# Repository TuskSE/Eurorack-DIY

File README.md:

View this project on [CADLAB.io](https://cadlab.io/project/24780). 

# Eurorack DIY
 An assortment of Schematics and PCB layouts for synthesizer modules in the Eurorack Format.  PCB layouts mostly use big surface mount parts ( e.g. SOIC IC's, 0804 passives ) except for electrolytics. I try as much as possible to limit the BOM to parts from Tayda Electronics - exceptions are mostly MCU boards and synthesizer-specific ICs. All schematic and PCB files are in KiCAD format, but not all have been updated yet for KiCAD v6. See below for a brief overview of projects.

# Modules

**Bandpass Filter **
A bank of 3 bandpass filters, with options mixing and phase inversion options. Schematics mostly complete, awaiting PCB layout. 

**CP3 Mixer**
A very generic transistor-type mixer. PCB layout complete, awaiting fabrication.

**Dual VCO**
A pair of utility VCOs/LFOs derived from the NonLinearCircuits Dual LFO/VCO, but with added FM inputs ( log on one, lin on the other ) and no sync inputs. PCB layout essentially finished, but I want to go back and rethink the voltage reference before sending it for fabrication.

**Fractional Clock Divider** 
A module to generate fractional divisions/multiplications of a clock signal and euclidean rhythms (which are basically fractional divisions, but quantized). The output can also be delayed / phase shifted. Built around a Teensy LC MCU board. This is "complete" and works, but in practise a lack of visual feedback in the UI makes it unintuitive and not fun to use - at some point I'll build something new and better around the same ideas. 

**Function Generator**
A variation on the Kassutronics slope, which in turn is a variation on the Serge Dual Universal Function Generator. The main notable addition is a hold input. PCB layout complete, awaiting fabrication. 

**Precision multiple**
4 buffered multiples: 2 are high-precision ( i.e. voltage is reproduced accurately enough to use for pitch CV ), all 4 have red/green LED indicators. There are only minor problems with the current PCB ( e.g. two of the LED footprints are the wrong way round ). 

**Threshold Logic Neuron** 
A Threshold Logic Neuron ( McCulloch–Pitts neuron ), inspired by a module from Analogue Research. In addition to serving as a programmable logic gate, the internal summing node has a dedicated output which can be used for the generation of stepwise CVs from boolean inputs. PCB layout just needs double-checking - otherwise, awaiting fabrication. 

**Precision Attenuverter**
A utility set of 4x attenuverters and cascading mixer, a.la fonitronik cascade. The first input can be calibrated so that "1x" attenuation ( knob fully CW ) is precise enough to use for pitch CV. The first batch of these had some PCB errors ( hard-to-solder footprints, back-to-front pots, etc ) which should be fixed in the current design ( March 2021 ), but I haven't fabbed it yet. I think the knob spacing is too tight - I plan to redo the layout with a wider spacing. 

**Stochastic sequencer**
A huge voltage sequencer project, incorporating elements of repeatable randomness ( like shift-register based sequencers ) and multiple steps per stage ( like the M185 sequencer / Intellijel Metropolis ). Each stage has its own independent voltage output, and the outputs are summed cascade-style until an input is plugged in. Multiple cycles can run in parallel over the 8 stages. The current version of the PCB ( v2 ) is working in terms of core functionality, but needs some minor tweaks. Most of the functionality is coded up, but after writing 1000s of lines of code I realized that the MCU ( Teensy LC ) RAM is insufficient for the functionality that I want, especially with regards to repeatable randomness. I believe the chip for the capacitive touch interface has also gone out of production. I'm still undecided whether to try again with a different MCU + capacitive touch chip, or whether to break the design up into smaller independent modules. 

**Tap LFO**
A clock-synced LFO built around the Electric Druid Tap LFO IC. The current version of the PCB layout only needs some small revisions, however I've abandoned it for now - in practise, I think it requires more visual feedback than can be accommodated with the Electric Druid IC. 

**Quad VCA**
A quad VCA built around the V2164 IC. Each channel has 2 CV attenuverters, one normalized to a 5V input. There's also a panning mixer integrated. v1 of the PCB had a couple of major issues which are awaiting correction. I think I may also rethink the control ranges etc.

**Pedal interface**
Designed as an interface between Eurorack and guitar pedals - schematic still under development. 

**Random trigger generator**
Barely started - still at the UI design phase 
 
# Case designs:

**"Big" case**
A console style case, 2 x 3U x 120HP, with space on top to mount more more cases.
Designed for laser cut 12mm plywood and standard Gie-tec rails.
I've built one of these - the glue up was a bit awkward with the non-square angle of the front piece, but otherwise it works fine and seems very solid. 

**"Test" case**
An 85HP rack with panel cutouts for current monitors and convenient terminals for oscilloscope/multimeter probes. In retrospect this is kind of a dumb idea when these things could have been added as, y'know, modules. A 1U row along the bottom instead would have been nice.
Designed for and laser cut from 5mm bamboo ply, which is attractive but honestly a bit flimsy, especially accross the grain.

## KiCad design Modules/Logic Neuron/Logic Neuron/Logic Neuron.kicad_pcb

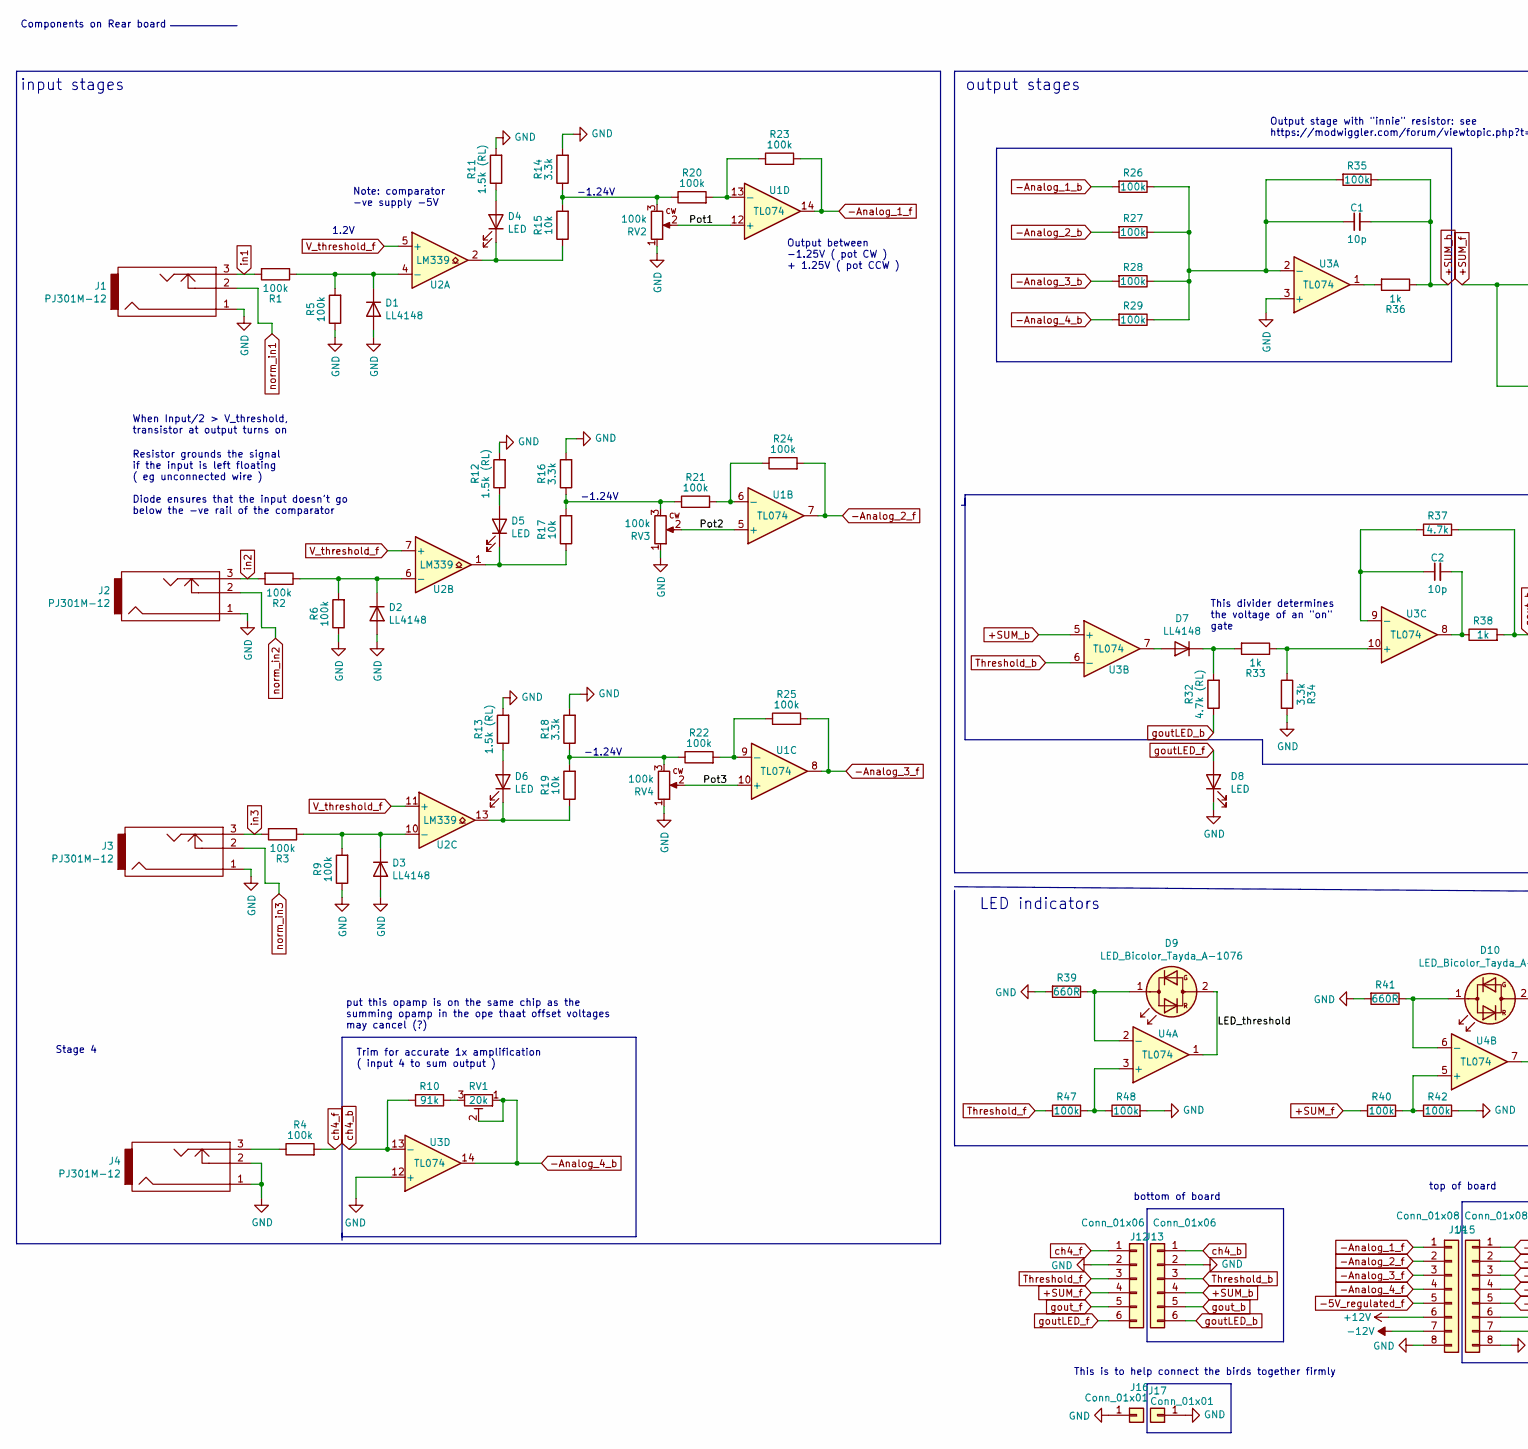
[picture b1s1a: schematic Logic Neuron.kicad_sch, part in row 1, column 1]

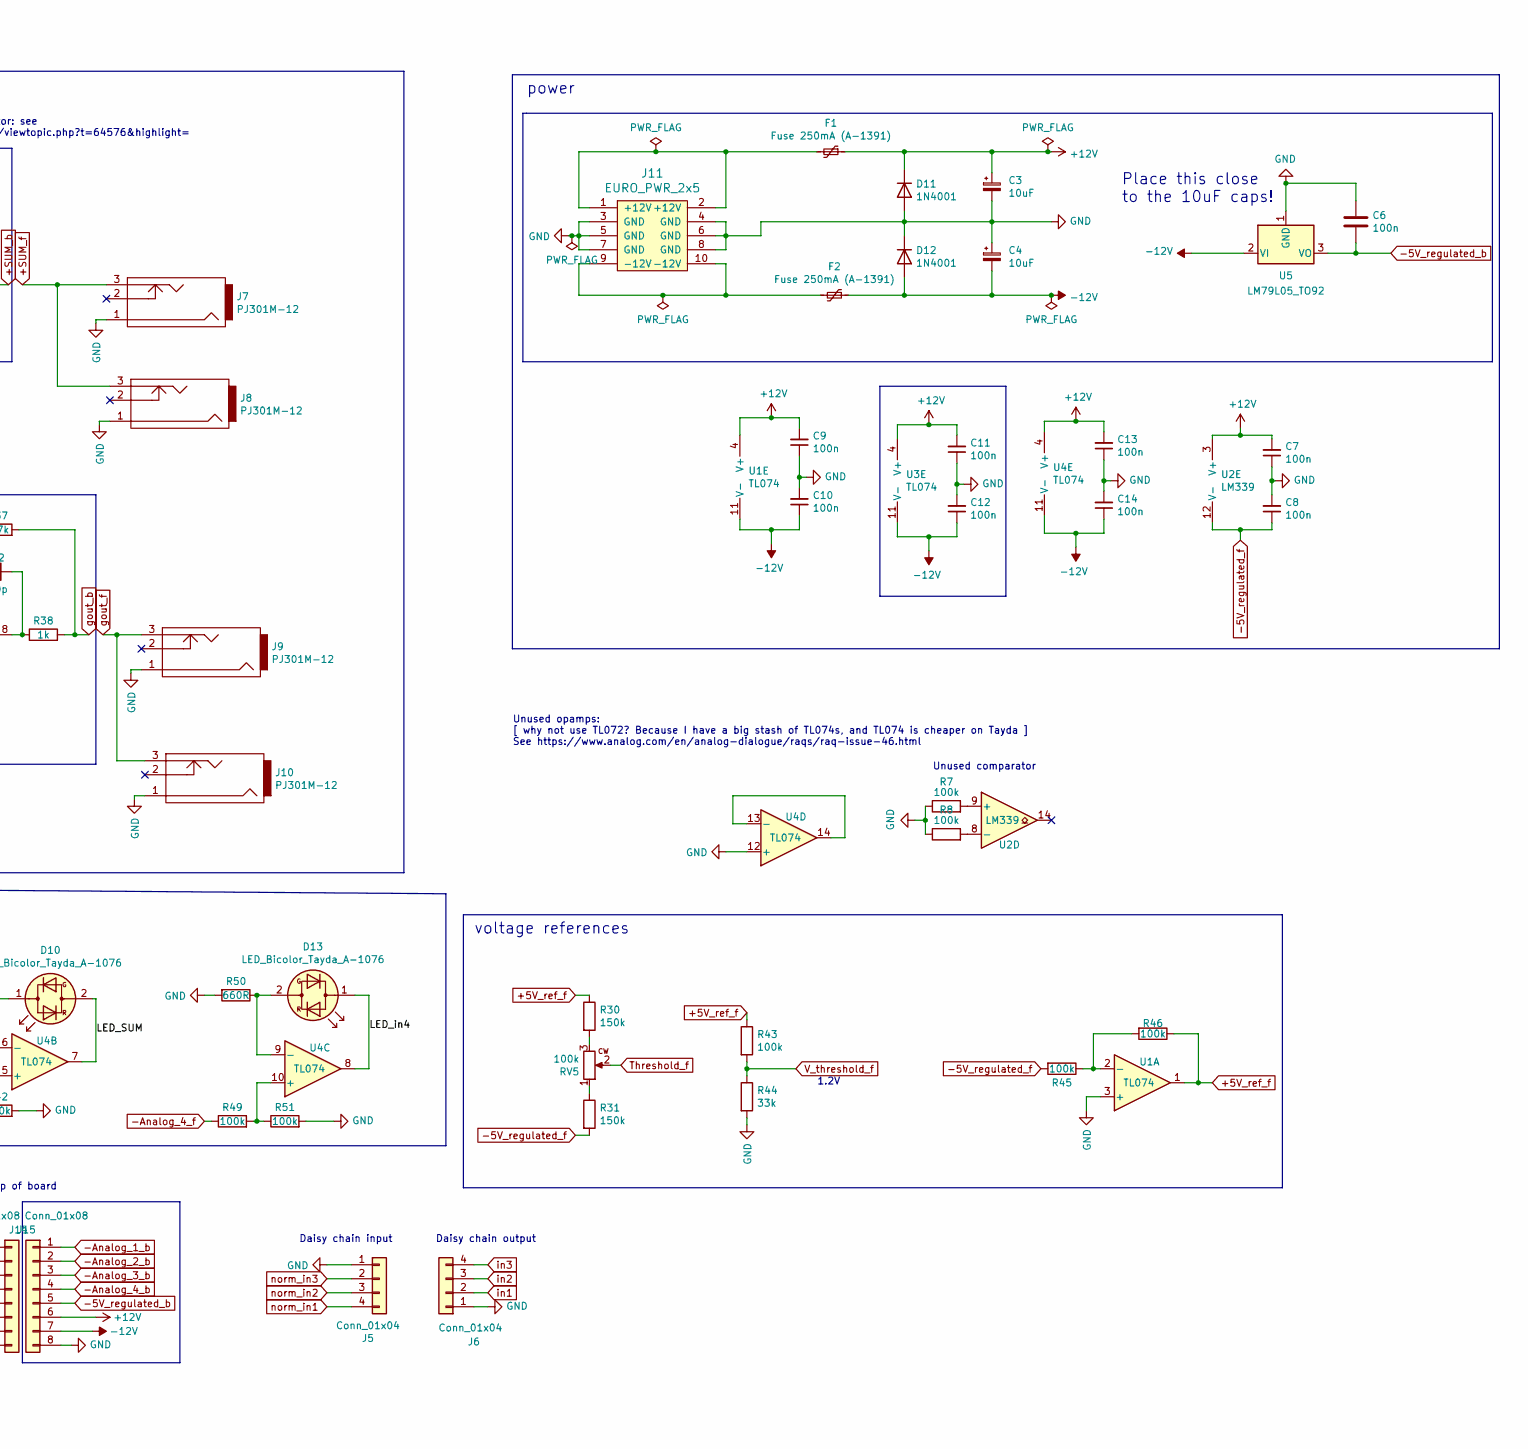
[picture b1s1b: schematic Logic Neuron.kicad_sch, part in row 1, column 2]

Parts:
C1, C2: 10p; C_0805_2012Metric_Pad1.15x1.40mm_HandSolder_SmallTxt
C3, C4: 10uF; CP_Radial_D5.0mm_P2.00mm
C6, C7, C8, C9, C10, C11, C12, C13, C14: 100n; C_0805_2012Metric_Pad1.15x1.40mm_HandSolder_SmallTxt
D1, D2, D3, D7: LL4148; LL4148_sam
D4, D5, D6, D8: LED; LED3mm
D9, D10, D13: LED_Bicolor_Tayda_A-1076; TaydaA-1076_bicolor_LED
D11, D12: 1N4001; D_DO-41_SOD81_P10.16mm_Horizontal
F1, F2: Fuse 250mA (A-1391); C_Disc_D7.5mm_W2.5mm_P5.00mm
J1, J2, J3, J4, J7, J8, J9, J10: PJ301M-12; PJ301M-12_Compact
J5, J6: Conn_01x04; PinHeader_1x04_P2.54mm_Vertical
J11: EURO_PWR_2x5; Eurorack_power_header
J12, J13: Conn_01x06; PinHeader_1x06_P2.54mm_Vertical
J14, J15: Conn_01x08; PinHeader_1x08_P2.54mm_Vertical
J16, J17: Conn_01x01; PinSocket_1x01_P2.54mm_Vertical
R1, R2, R3, R4, R5, R6, R7, R8, R9, R20, R21, R22, R23, R24, R25, R26, R27, R28, R29, R35, R40, R42, R43, R45, R46, R47, R48, R49, R51: 100k; R_0805_2012Metric_Pad1.15x1.40mm_HandSolder_smallText
R10: 91k; R_0805_2012Metric_Pad1.15x1.40mm_HandSolder_smallText
R11, R12, R13: 1.5k (RL); R_0805_2012Metric_Pad1.15x1.40mm_HandSolder_smallText
R14, R16, R18, R34: 3.3k; R_0805_2012Metric_Pad1.15x1.40mm_HandSolder_smallText
R15, R17, R19: 10k; R_0805_2012Metric_Pad1.15x1.40mm_HandSolder_smallText
R30, R31: 150k; R_0805_2012Metric_Pad1.15x1.40mm_HandSolder_smallText
R32: 4.7k (RL); R_0805_2012Metric_Pad1.15x1.40mm_HandSolder_smallText
R33, R36, R38: 1k; R_0805_2012Metric_Pad1.15x1.40mm_HandSolder_smallText
R37: 4.7k; R_0805_2012Metric_Pad1.15x1.40mm_HandSolder_smallText
R39, R41, R50: 660R; R_0805_2012Metric_Pad1.15x1.40mm_HandSolder_smallText
R44: 33k; R_0805_2012Metric_Pad1.15x1.40mm_HandSolder_smallText
RV1: 20k; Potentiometer_Bourns_3296W_Vertical
RV2, RV3, RV4, RV5: 100k; Alpha9mmPot
U1, U3, U4: TL074; SOIC-14_3.9x8.7mm_P1.27mm
U2: LM339; SOIC-14_3.9x8.7mm_P1.27mm
U5: LM79L05_TO92; TO-92_HandSolder

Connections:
+5V_ref_f: R30.1, R43.1, R46.1, U1.1
+12V: C3.1, C7.2, C9.2, C11.2, C13.2, D11.1 (K), F1.1, J14.6, J15.6, U1.4 (V+), U2.3 (V+), U3.4 (V+), U4.4 (V+)
+SUM_b: C1.2, J13.4, R35.1, R36.1, U3.5 (+)
+SUM_f: J7.3, J8.3, J12.4, R40.1
-5V_regulated_b: C6.2, J15.5, U5.3 (VO)
-5V_regulated_f: C8.1, J14.5, R31.2, R45.2, U2.12 (V-)
-12V: C4.2, C10.1, C12.1, C14.1, D12.2 (A), F2.1, J14.7, J15.7, U1.11 (V-), U3.11 (V-), U4.11 (V-), U5.2 (VI)
-Analog_1_b: J15.1, R26.2
-Analog_1_f: J14.1, R23.2, U1.14
-Analog_2_b: J15.2, R27.2
-Analog_2_f: J14.2, R24.2, U1.7
-Analog_3_b: J15.3, R28.2
-Analog_3_f: J14.3, R25.2, U1.8
-Analog_4_b: J15.4, R29.2, RV1.1, RV1.2, U3.14
-Analog_4_f: J14.4, R49.1
/LED_SUM: D10.2 (AK), U4.7
/LED_in4: D13.1 (KA), U4.8
/LED_threshold: D9.2 (AK), U4.1
/Pot1: RV2.2, U1.12 (+)
/Pot2: RV3.2, U1.5 (+)
/Pot3: RV4.2, U1.10 (+)
GND: C3.2, C4.1, C6.1, C7.1, C8.2, C9.1, C10.2, C11.1, C12.2, C13.1, C14.2, D1.2 (A), D2.2 (A), D3.2 (A), D8.1 (K), D11.2 (A), D12.1 (K), J1.1, J2.1, J3.1, J4.1, J4.2, J5.1, J6.1, J7.1, J8.1, J9.1, J10.1, J11.3 (GND), J11.4 (GND), J11.5 (GND), J11.6 (GND), J11.7 (GND), J11.8 (GND), J12.2, J13.2, J14.8, J15.8, J16.1, J17.1, R5.1, R6.1, R7.1, R8.1, R9.1, R11.2, R12.2, R13.2, R14.2, R16.2, R18.2, R34.2, R39.2, R41.2, R42.2, R44.2, R48.2, R50.2, R51.2, RV2.1, RV3.1, RV4.1, U1.3 (+), U3.3 (+), U3.12 (+), U4.12 (+), U5.1 (GND)
unnamed: C1.1, R26.1, R27.1, R28.1, R29.1, R35.2, U3.2 (-)
unnamed: C2.1, R37.1, U3.9 (-)
unnamed: C2.2, R38.1, U3.8
unnamed: D1.1 (K), R1.1, R5.2, U2.4 (-)
unnamed: D2.1 (K), R2.1, R6.2, U2.6 (-)
unnamed: D3.1 (K), R3.1, R9.2, U2.10 (-)
unnamed: D4.1 (K), R15.1, U2.2
unnamed: D4.2 (A), R11.1
unnamed: D5.1 (K), R17.1, U2.1
unnamed: D5.2 (A), R12.1
unnamed: D6.1 (K), R19.1, U2.13
unnamed: D6.2 (A), R13.1
unnamed: D7.1 (K), R32.2, R33.2
unnamed: D7.2 (A), U3.7
unnamed: D9.1 (KA), R39.1, U4.2 (-)
unnamed: D10.1 (KA), R41.1, U4.6 (-)
unnamed: D13.2 (AK), R50.1, U4.9 (-)
unnamed: F1.2, J11.1 (+12V), J11.2 (+12V)
unnamed: F2.2, J11.9 (-12V), J11.10 (-12V)
unnamed: J4.3, R4.1
unnamed: R7.2, U2.9 (+)
unnamed: R8.2, U2.8 (-)
unnamed: R10.1, RV1.3
unnamed: R14.1, R15.2, R20.1, RV2.3
unnamed: R16.1, R17.2, R21.1, RV3.3
unnamed: R18.1, R19.2, R22.1, RV4.3
unnamed: R20.2, R23.1, U1.13 (-)
unnamed: R21.2, R24.1, U1.6 (-)
unnamed: R22.2, R25.1, U1.9 (-)
unnamed: R30.2, RV5.3
unnamed: R31.1, RV5.1
unnamed: R33.1, R34.1, U3.10 (+)
unnamed: R36.2, U3.1
unnamed: R40.2, R42.1, U4.5 (+)
unnamed: R45.1, R46.2, U1.2 (-)
unnamed: R47.2, R48.1, U4.3 (+)
unnamed: R49.2, R51.1, U4.10 (+)
unnamed: U4.13 (-), U4.14
Threshold_b: J13.3, U3.6 (-)
Threshold_f: J12.3, R47.1, RV5.2
V_threshold_f: R43.2, R44.1, U2.5 (+), U2.7 (+), U2.11 (+)
ch4_b: J13.1, R10.2, U3.13 (-)
ch4_f: J12.1, R4.2
goutLED_b: J13.6, R32.1
goutLED_f: D8.2 (A), J12.6
gout_b: J13.5, R37.2, R38.2
gout_f: J9.3, J10.3, J12.5
in1: J1.3, J6.2, R1.2
in2: J2.3, J6.3, R2.2
in3: J3.3, J6.4, R3.2
norm_in1: J1.2, J5.4
norm_in2: J2.2, J5.3
norm_in3: J3.2, J5.2

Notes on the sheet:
Trim for accurate 1x amplification ( input 4 to sum output )
-1.24V
voltage references
bottom of board
Unused comparator
input stages
output stages
Unused opamps: [ why not use TL072? Because I have a big stash of TL074s, and TL074 is cheaper on Tayda ] See https://www.analog.com/en/analog-dialogue/raqs/raq-issue-46.html
Stage 4
This is to help connect the birds together firmly
put this opamp is on the same chip as the summing opamp in the ope thaat offset voltages may cancel (?)
top of board
LED indicators
1.2V
Output stage with "innie" resistor: see https://modwiggler.com/forum/viewtopic.php?t=64576&highlight=
Note: comparator -ve supply -5V
When Input/2 > V_threshold, transistor at output turns on
This divider determines the voltage of an "on" gate
Daisy chain output
Daisy chain input
Place this close to the 10uF caps!
Components on Rear board
power
Resistor grounds the signal if the input is left floating ( eg unconnected wire ) Diode ensures that the input doesn't go below the -ve rail of the comparator
Output between -1.25V ( pot CW ) + 1.25V ( pot CCW )

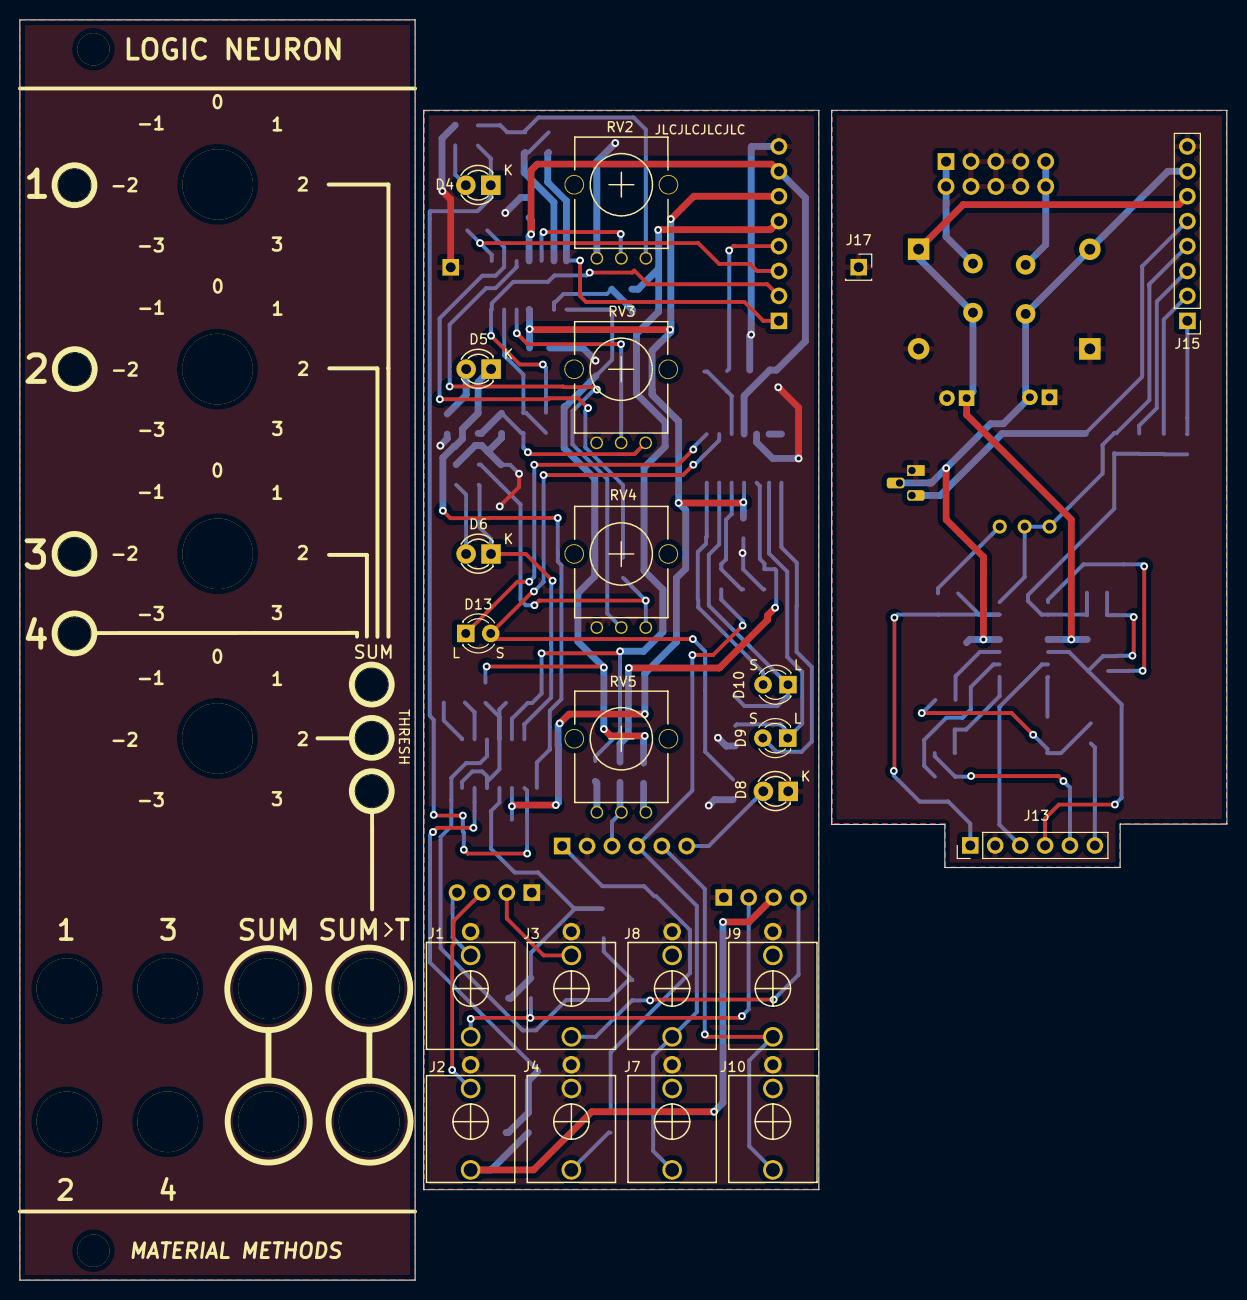
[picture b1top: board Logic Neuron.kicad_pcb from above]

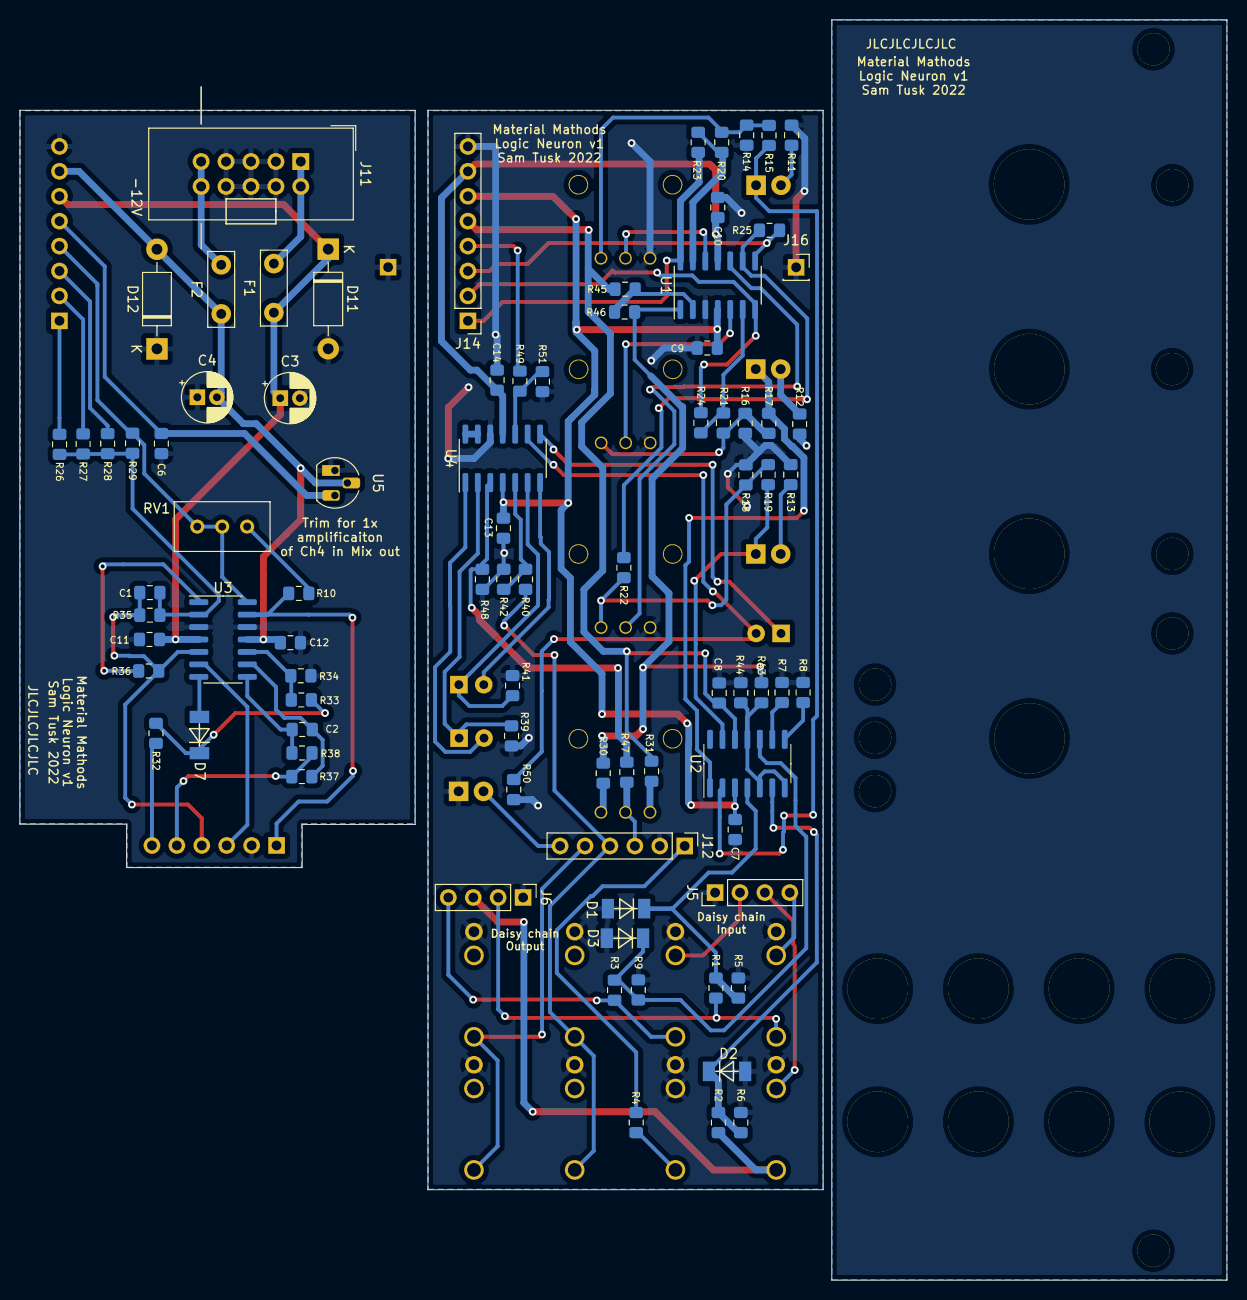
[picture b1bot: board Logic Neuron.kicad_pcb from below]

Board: 2 copper layers, 123.1 x 128.5 mm, 118 parts (84 on the bottom side), 75 nets.

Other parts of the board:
Ref**: Pothole_Davies1900H_white
Ref**#2, Ref**#12: Pothole_Davies1900H_white
Ref**#3: Pothole_Davies1900H_red
Ref**#4, Ref**#5, Ref**#6, Ref**#7, Ref**#8, Ref**#9, Ref**#10, Ref**#11: Eurorack jack hole; Eurorack_jack_hole
